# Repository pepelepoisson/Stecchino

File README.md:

***
Stecchino is an home-made game where you need to balance a stick-like device at the tip of your fingers. The longer you can keep it balanced the more LEDs are lit on the Stecchino device. Can you do better than your friends?

***

More details, photos and videos at http://www.chezpapietmamie.com/pcube/arduino/stecchino/
***
This repo contains:
- Arduino Pro Mini sketch
- Electronic schematic, V1 PCB KiCad files and Gerbers
- Laser cut Inkscape and pdf files for V4 plywood Stecchino
***
Bill Of Material and costs for PCB V1:

|Quantity|Description|Unit cost (CAD)|Cost(CAD)|Example reference|
|--------|-----------|---------|----|-----------------|
|1|Arduino Pro Mini 3.3V 16MHz|3,11|3,11|https://fr.aliexpress.com/item/Freeshipping-1pcs-lot-Pro-Mini-328-Mini-3-3V-16M-ATMEGA328-3-3V-16MHz-for-arduino/32695657337.html|
|1|MPU6050 accelerometer board|2|2|https://fr.aliexpress.com/item/MPU-6050-3-Axis-gyroscope-acce-lerometer-module-3V-5V-compatible-For-Arduino/2035920870.html|
|1|LiPo management board|2,4|2,4|https://fr.aliexpress.com/item/5-pcs-Micro-USB-5V-1A-18650-TP4056-Lithium-Battery-Charger-Module-Charging-Board-With-Protection/32703936097.html|
|2|Small push button|0,1|0,2|https://fr.aliexpress.com/item/Promotion-Amico-100-Pcs-6x6x4-5mm-Panel-PCB-Momentary-Tactile-Tact-Push-Button-Switch-4-Pin/32563399489.html|
|2|10K resistor|0,1|0,2||
|1|IRF9540 Mosfet|0,4|0,4||
|1|NPN transistor 2N3904|0,25|0,25||
|1|1x2 90 deg pin headers|0,2|0,2||
|1|1x3 90 deg pin headers|0,2|0,2||
|1|LiPo battery|4|4|https://fr.aliexpress.com/item/5pcs-lot-Syma-X5C-X5SW-Heng-Kee-905-Cherson-CX-30-model-aircraft-Tanco-M68-3/32603900524.html|
|1|50cm 72 WS2812B LEDs strip|10,515|10,515|https://fr.aliexpress.com/item/individually-addressable-1m-4m-5m-waterproof-ip65-ip67-5050-rgb-30-60-144-led-m-5v/32773441024.html|
|1|PCB|2|2||

Total: Approx 25.5CAD for electronics + cost of woodwork.

Make one yourself and let me know!
***

***
A few measurements to establish minimum VCC before Stecchino starts to bug. 

***

***

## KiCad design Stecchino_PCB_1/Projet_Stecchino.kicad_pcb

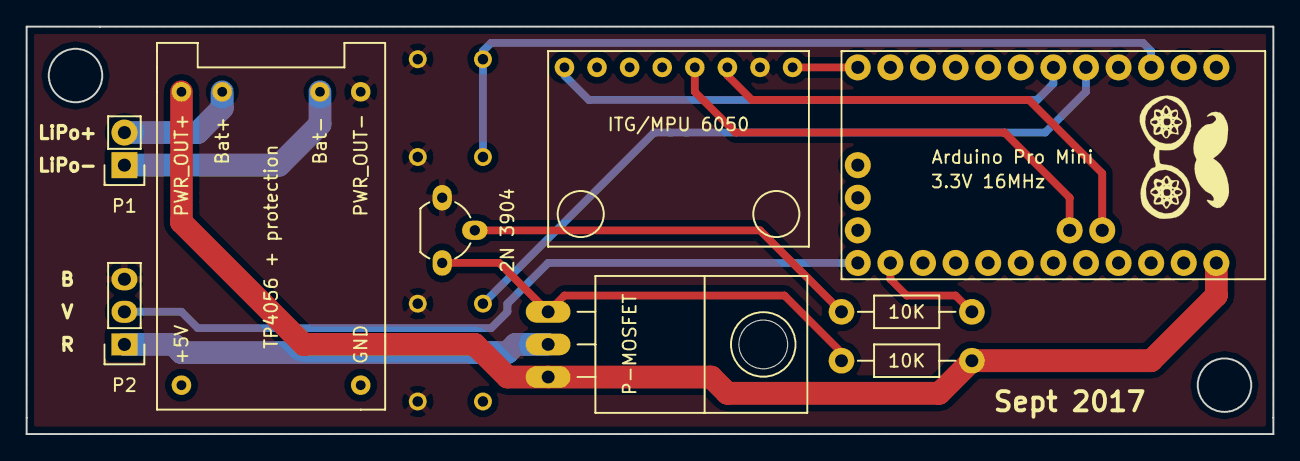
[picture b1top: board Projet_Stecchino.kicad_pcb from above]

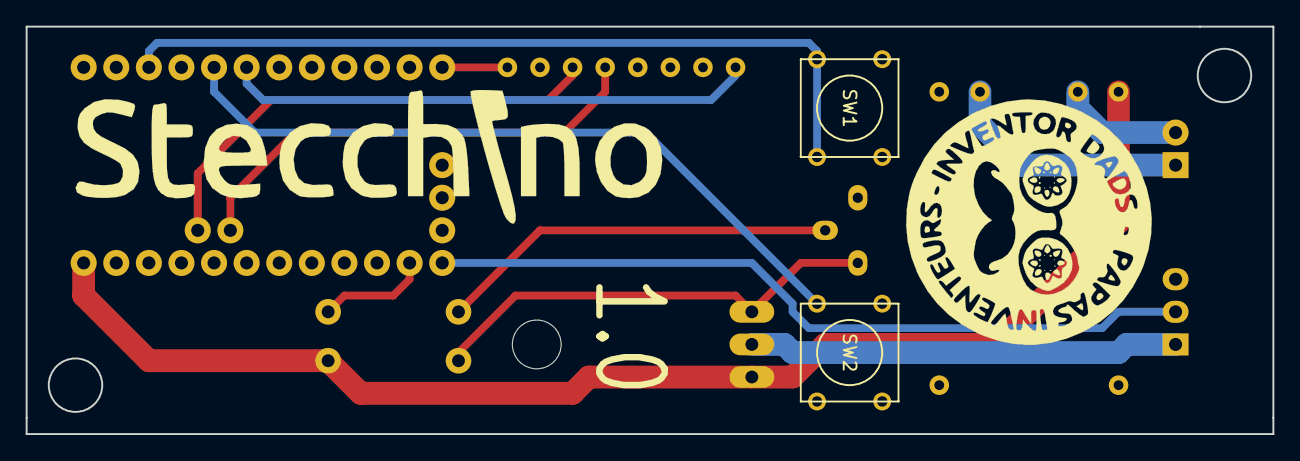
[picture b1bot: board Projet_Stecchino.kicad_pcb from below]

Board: 2 copper layers, 97.2 x 31.8 mm, 11 parts (2 on the bottom side), 15 nets.

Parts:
2N 3904: 2N3904; TO-92_Molded_Wide_Oval
3.3V 16MHz: ARDUPROMINI_pins_on_4_sides; ArduinoProMini_pins_on_3_sides_big_holes
10K, 10K#2: 10K; Resistor_Horizontal_RM10mm
ITG/MPU 6050: ITG/MPU6050; ITG_MPU_6050
P1: CONN_01X02; Pin_Header_Straight_1x02
P2: CONN_01X03; Pin_Header_Straight_1x03
P-MOSFET: IRF9540; TO-220_Neutral123_Horizontal_LargePads
SW1, SW2: SW_PUSH; SW_PUSH_SMALL
TP4056 + protection: LiPo_Mngmt_Board

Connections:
+BATT: 3.3V 16MHz.19, 10K#2.2, P-MOSFET.3, TP4056 + protection.4
/D2: 3.3V 16MHz.11, SW2.2
/D3: 3.3V 16MHz.12, ITG/MPU 6050.8
/I2C_SCL: 3.3V 16MHz.31, ITG/MPU 6050.3
/I2C_SDA: 3.3V 16MHz.32, ITG/MPU 6050.4
/ITG/MPU_VCC: 3.3V 16MHz.18, ITG/MPU 6050.1
/LIPO+: P1.2, TP4056 + protection.1
/LIPO-: P1.1, TP4056 + protection.2
/MOSFET_PIN: 3.3V 16MHz.29, 10K.2
/RESET: 3.3V 16MHz.9, SW1.2
/WS_DATA_IN: 3.3V 16MHz.30, P2.2
GND: 2N 3904.1, 3.3V 16MHz.10, ITG/MPU 6050.2, P2.3, SW1.1, SW2.1, TP4056 + protection.3
unnamed: P2.1, P-MOSFET.2
unnamed: 2N 3904.2, 10K.1
unnamed: 2N 3904.3, 10K#2.1, P-MOSFET.1

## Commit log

2017-09-11 add images
2017-09-11 testing README.md
2017-09-11 updating README.md
2017-09-18 Added timer and ligth effects to make ganme entirely usable
2017-10-09 added spirit level mode + fake sleep + angle_2_horizon
2018-03-09 Added battery check routine + allowed idle pattern changes + ensure sleep after a while at idle
2018-03-10 Minor code changes + added V1.0 PCB files + V4.0 laser cut files
2018-03-17 Added copies of Arduino librairies used + PCB V1 schematic
2018-03-17 Attempting to edit README.md
2018-03-18 New image
2018-03-24 NResized images
2018-03-24 Corrected error in LEDs strip link on BOM table
2018-05-10 Fix buffer overflows.
2018-11-14 Minor changes to PCB to increase hole diameters for mpu and lipo management board
